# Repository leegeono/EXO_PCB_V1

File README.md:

# EXO_PCB_V1

## Overview
First prototype PCB for motor control experiments.

## Hardware
- ESCON Motor Driver x4
- Teensy 4.1
- Battery Input (3S ~ 6S)
- 5V Regulator
- nano rp2040

 ## Purpose
- Motor control study
- PCB design practice
- Power distribution testing
- Embedded system integration

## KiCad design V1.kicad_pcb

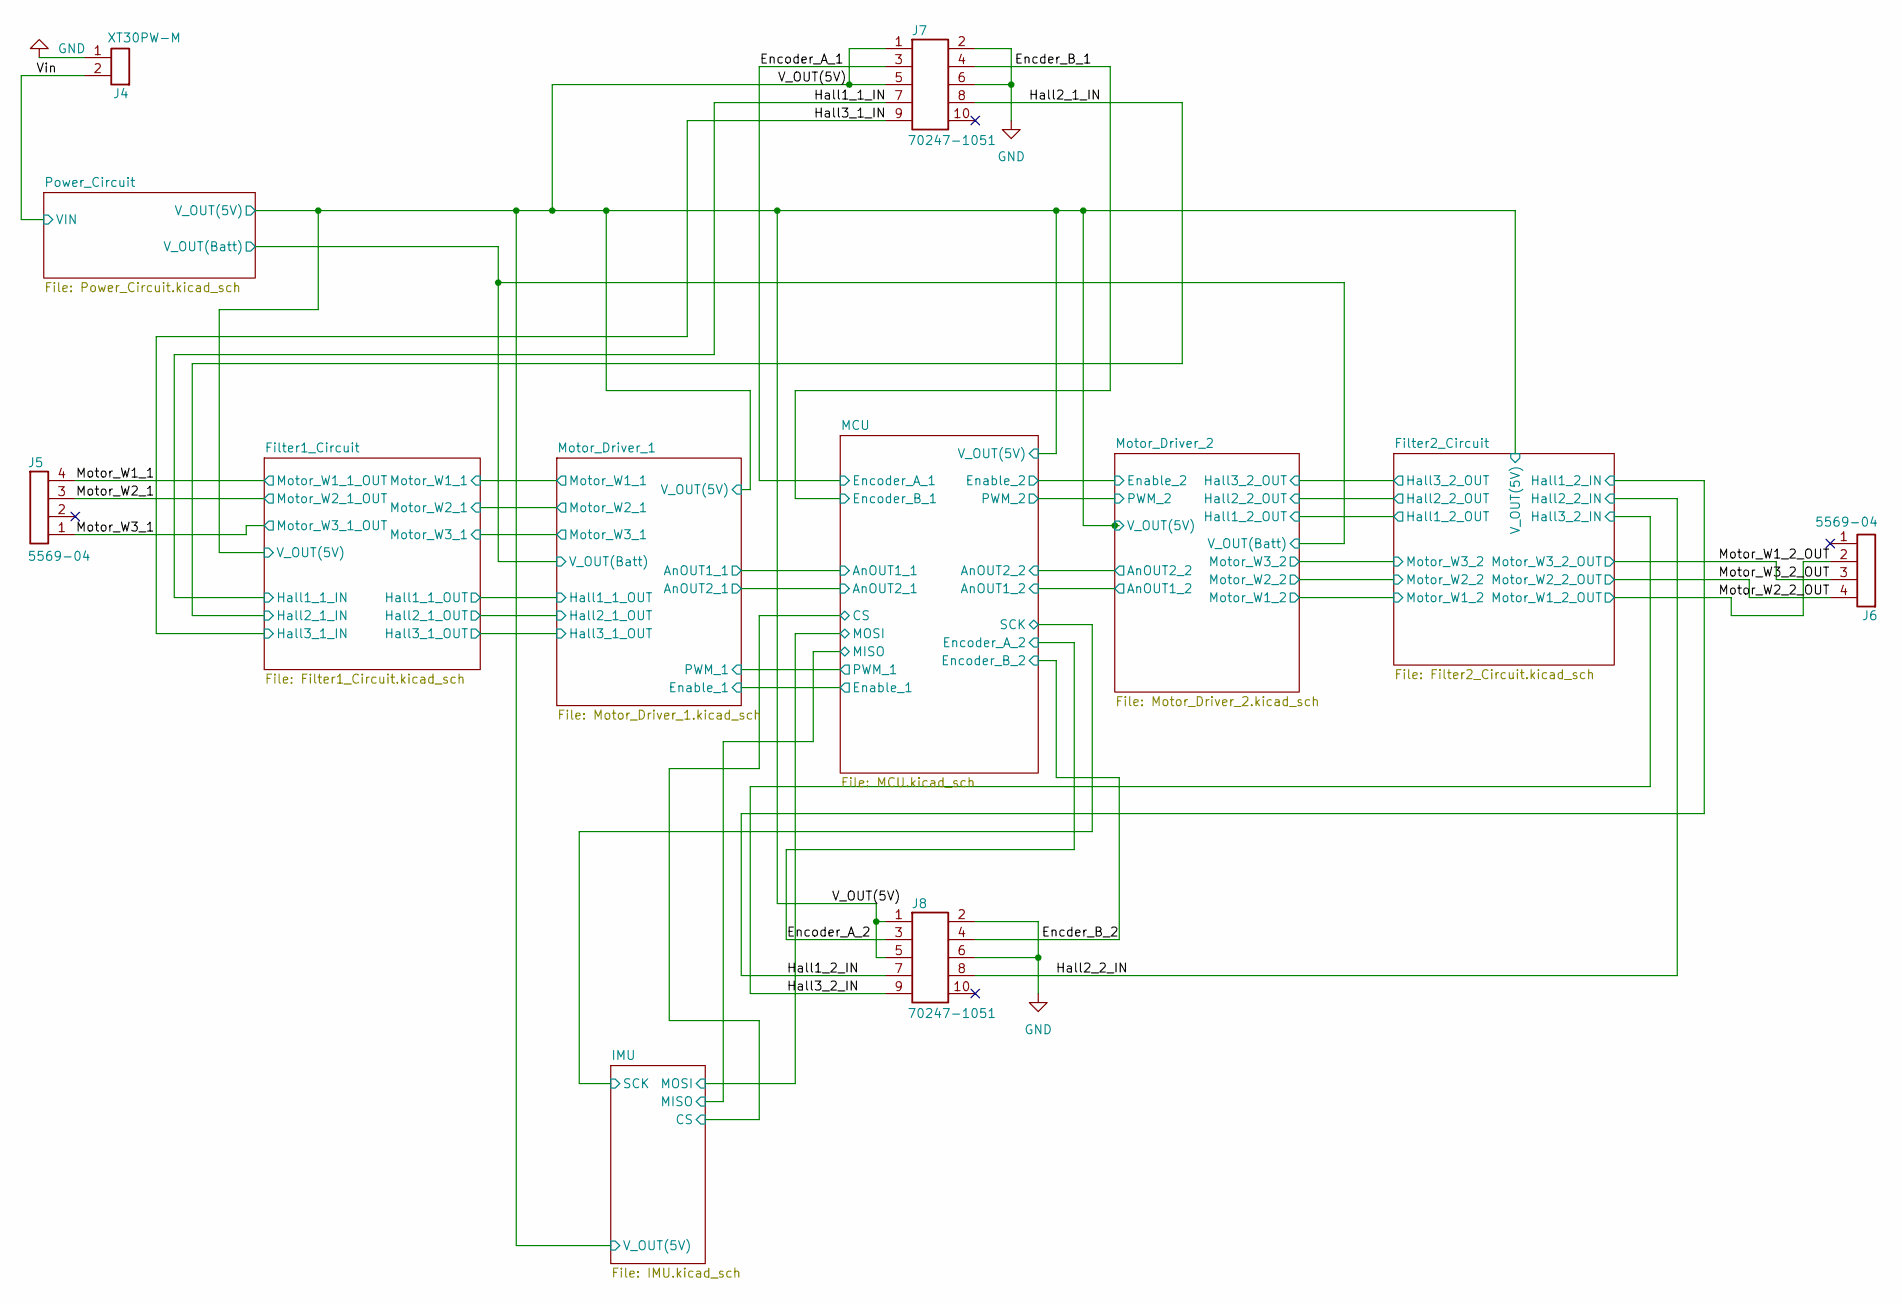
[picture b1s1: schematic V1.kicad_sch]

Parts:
J4: XT30PW-M
J5, J6: 5569-04
J7, J8: 70247-1051

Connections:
/Encder_B_1: J7.4 (Pin_9); also elsewhere on the board
/Encder_B_2: J8.4 (Pin_9); also elsewhere on the board
/Encoder_A_1: J7.3 (Pin_2); also elsewhere on the board
/Encoder_A_2: J8.3 (Pin_2); also elsewhere on the board
/Hall1_1_IN: J7.7 (Pin_4); also elsewhere on the board
/Hall1_2_IN: J8.7 (Pin_4); also elsewhere on the board
/Hall2_1_IN: J7.8 (Pin_7); also elsewhere on the board
/Hall2_2_IN: J8.8 (Pin_7); also elsewhere on the board
/Hall3_1_IN: J7.9; also elsewhere on the board
/Hall3_2_IN: J8.9; also elsewhere on the board
/Motor_W1_1: J5.4; also elsewhere on the board
/Motor_W1_2_OUT: J6.2; also elsewhere on the board
/Motor_W2_1: J5.3; also elsewhere on the board
/Motor_W2_2_OUT: J6.4; also elsewhere on the board
/Motor_W3_1: J5.1; also elsewhere on the board
/Motor_W3_2_OUT: J6.3; also elsewhere on the board
/V_OUT(5V): J7.1, J7.5 (Pin_3), J8.1, J8.5 (Pin_3); also elsewhere on the board
/Vin: J4.2; also elsewhere on the board
GND: J4.1, J7.2 (Pin_10), J7.6 (Pin_8), J8.2 (Pin_10), J8.6 (Pin_8); also elsewhere on the board

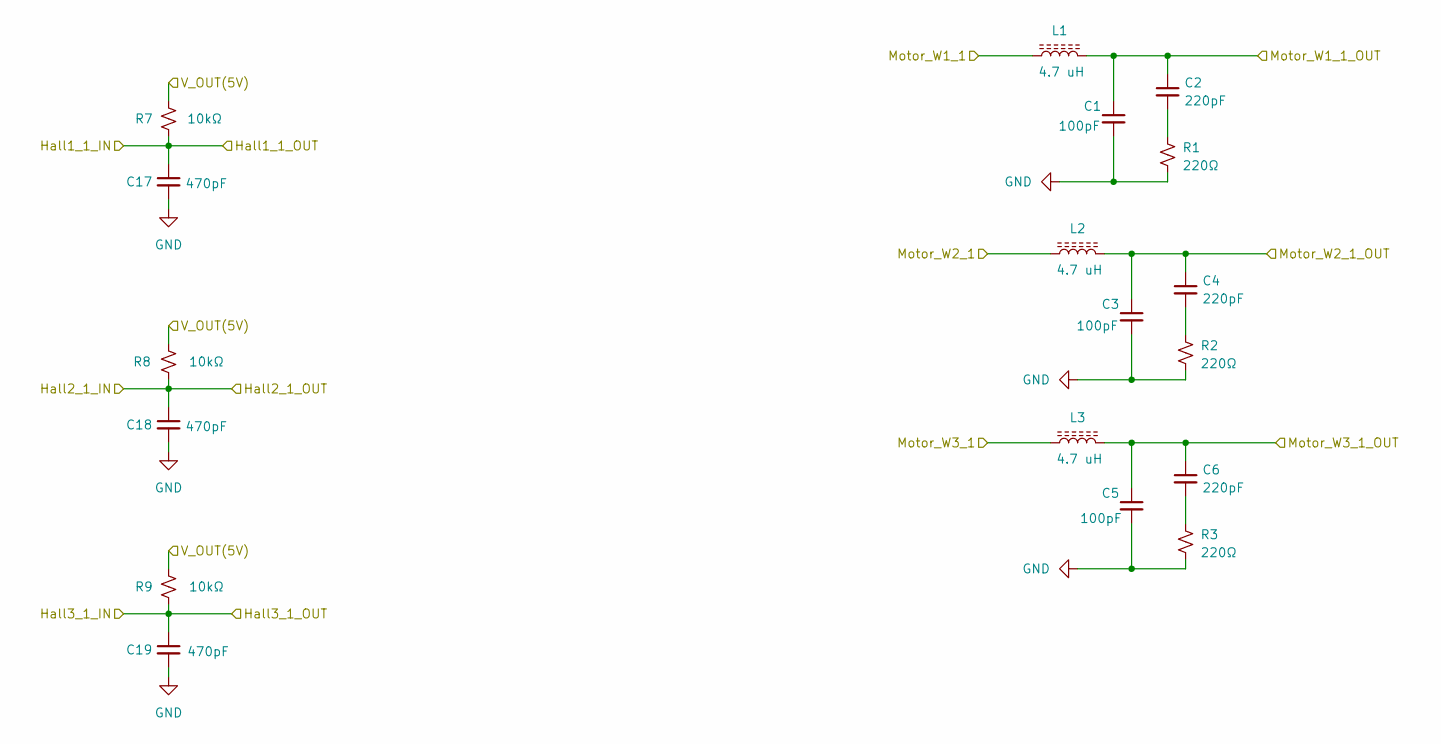
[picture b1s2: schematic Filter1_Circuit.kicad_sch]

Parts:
C1, C3, C5: 100pF; C_0603_1608Metric
C2, C4, C6: 220pF; C_0603_1608Metric
C17, C18, C19: 470pF; C_0603_1608Metric
L1, L2, L3: 4.7 uH; WE-PD_1260_1245_1280_121054
R1, R2, R3: 220Ω; R_1206_3216Metric
R7, R8, R9: 10kΩ; R_0603_1608Metric

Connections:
/Filter1_Circuit/Motor_W1_1: L1.1; also elsewhere on the board
/Filter1_Circuit/Motor_W2_1: L2.1; also elsewhere on the board
/Filter1_Circuit/Motor_W3_1: L3.1; also elsewhere on the board
/Hall1_1_IN: C17.1, R7.2; also elsewhere on the board
/Hall2_1_IN: C18.1, R8.2; also elsewhere on the board
/Hall3_1_IN: C19.1, R9.2; also elsewhere on the board
/Motor_W1_1: C1.1, C2.1, L1.2; also elsewhere on the board
/Motor_W2_1: C3.1, C4.1, L2.2; also elsewhere on the board
/Motor_W3_1: C5.1, C6.1, L3.2; also elsewhere on the board
/V_OUT(5V): R7.1, R8.1, R9.1; also elsewhere on the board
GND: C1.2, C3.2, C5.2, C17.2, C18.2, C19.2, R1.2, R2.2, R3.2; also elsewhere on the board
unnamed: C2.2, R1.1
unnamed: C4.2, R2.1
unnamed: C6.2, R3.1

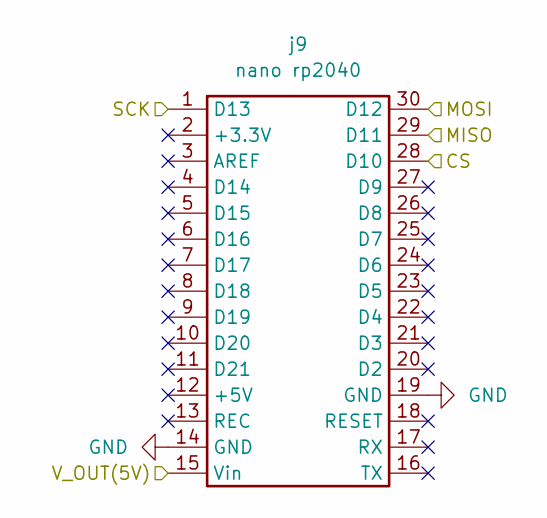
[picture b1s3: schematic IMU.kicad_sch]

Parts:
j9: nano rp2040; nano_rp2040

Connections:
/IMU/CS: j9.28 (D10); also elsewhere on the board
/IMU/MISO: j9.29 (D11); also elsewhere on the board
/IMU/MOSI: j9.30 (D12); also elsewhere on the board
/IMU/SCK: j9.1 (D13); also elsewhere on the board
/V_OUT(5V): j9.15 (Vin); also elsewhere on the board
GND: j9.14 (GND), j9.19 (GND); also elsewhere on the board

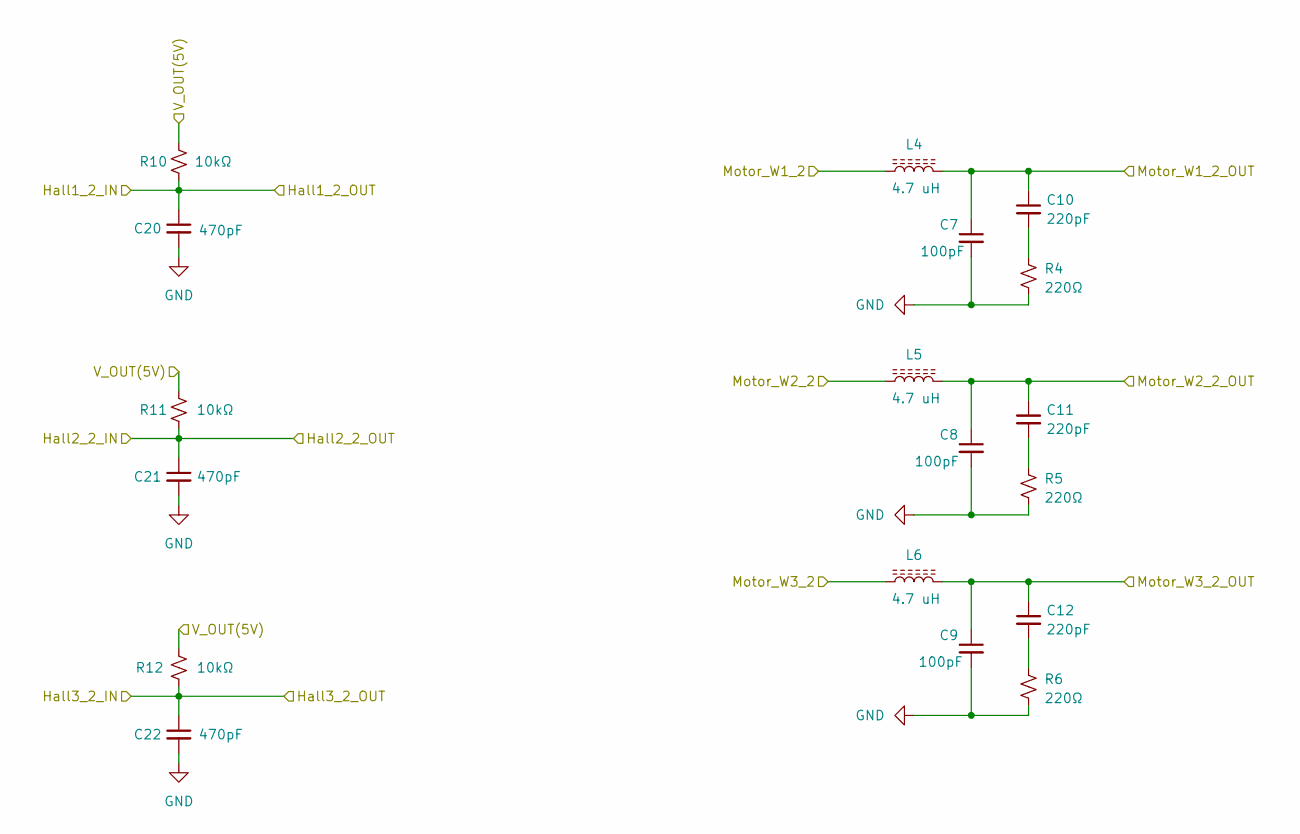
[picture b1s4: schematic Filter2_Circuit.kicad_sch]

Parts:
C7, C8, C9: 100pF; C_0603_1608Metric
C10, C11, C12: 220pF; C_0603_1608Metric
C20, C21, C22: 470pF; C_0603_1608Metric
L4, L5, L6: 4.7 uH; WE-PD_1260_1245_1280_121054
R4, R5, R6: 220Ω; R_1206_3216Metric
R10, R11, R12: 10kΩ; R_0603_1608Metric

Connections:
/Filter2_Circuit/Motor_W1_2: L4.1; also elsewhere on the board
/Filter2_Circuit/Motor_W2_2: L5.1; also elsewhere on the board
/Filter2_Circuit/Motor_W3_2: L6.1; also elsewhere on the board
/Hall1_2_IN: C20.1, R10.2; also elsewhere on the board
/Hall2_2_IN: C21.1, R11.2; also elsewhere on the board
/Hall3_2_IN: C22.1, R12.2; also elsewhere on the board
/Motor_W1_2_OUT: C7.1, C10.1, L4.2; also elsewhere on the board
/Motor_W2_2_OUT: C8.1, C11.1, L5.2; also elsewhere on the board
/Motor_W3_2_OUT: C9.1, C12.1, L6.2; also elsewhere on the board
/V_OUT(5V): R10.1, R11.1, R12.1; also elsewhere on the board
GND: C7.2, C8.2, C9.2, C20.2, C21.2, C22.2, R4.2, R5.2, R6.2; also elsewhere on the board
unnamed: C10.2, R4.1
unnamed: C11.2, R5.1
unnamed: C12.2, R6.1

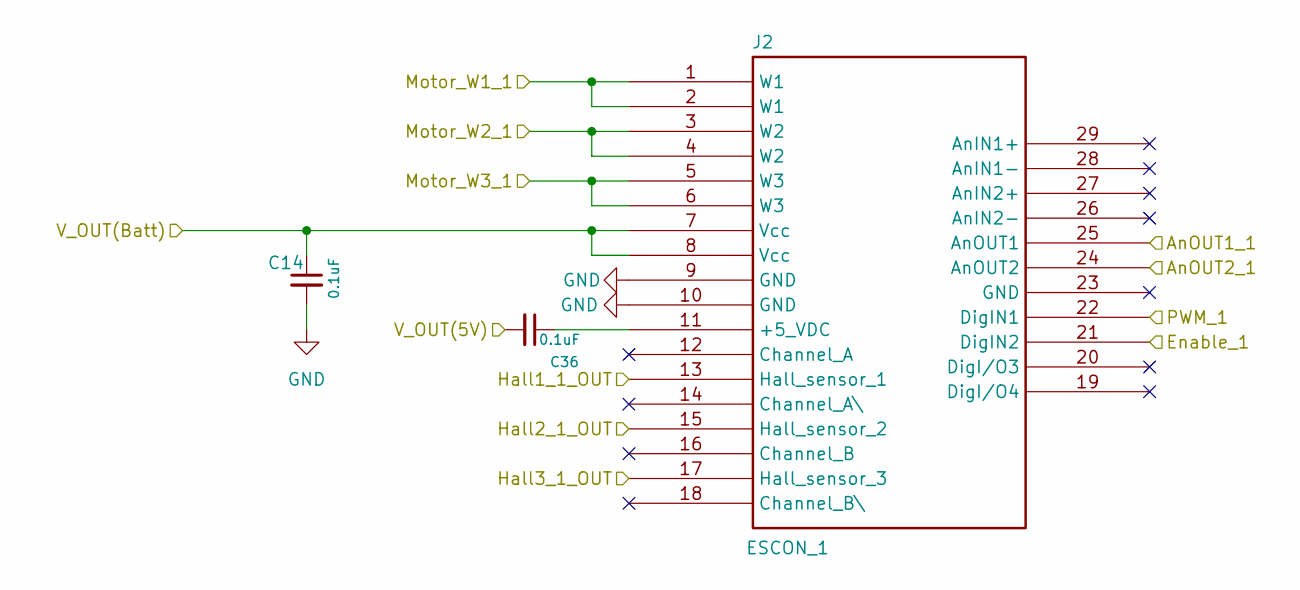
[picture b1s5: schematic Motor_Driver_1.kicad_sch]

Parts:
C14, C36: 0.1uF; C_0603_1608Metric
J2: ESCON_1; Escon 50,8

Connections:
/Filter1_Circuit/Motor_W1_1: J2.1 (W1), J2.2 (W1); also elsewhere on the board
/Filter1_Circuit/Motor_W2_1: J2.3 (W2), J2.4 (W2); also elsewhere on the board
/Filter1_Circuit/Motor_W3_1: J2.5 (W3), J2.6 (W3); also elsewhere on the board
/Hall1_1_IN: J2.13 (Hall_sensor_1); also elsewhere on the board
/Hall2_1_IN: J2.15 (Hall_sensor_2); also elsewhere on the board
/Hall3_1_IN: J2.17 (Hall_sensor_3); also elsewhere on the board
/MCU/AnOUT1_1: J2.25 (AnOUT1); also elsewhere on the board
/MCU/AnOUT2_1: J2.24 (AnOUT2); also elsewhere on the board
/MCU/Enable_1: J2.21 (DigIN2); also elsewhere on the board
/MCU/PWM_1: J2.22 (DigIN1); also elsewhere on the board
/Motor_Driver_1/V_OUT(Batt): C14.1, J2.7 (Vcc), J2.8 (Vcc); also elsewhere on the board
/V_OUT(5V): C36.2; also elsewhere on the board
GND: C14.2, J2.9 (GND), J2.10 (GND); also elsewhere on the board
unnamed: C36.1, J2.11 (+5_VDC)

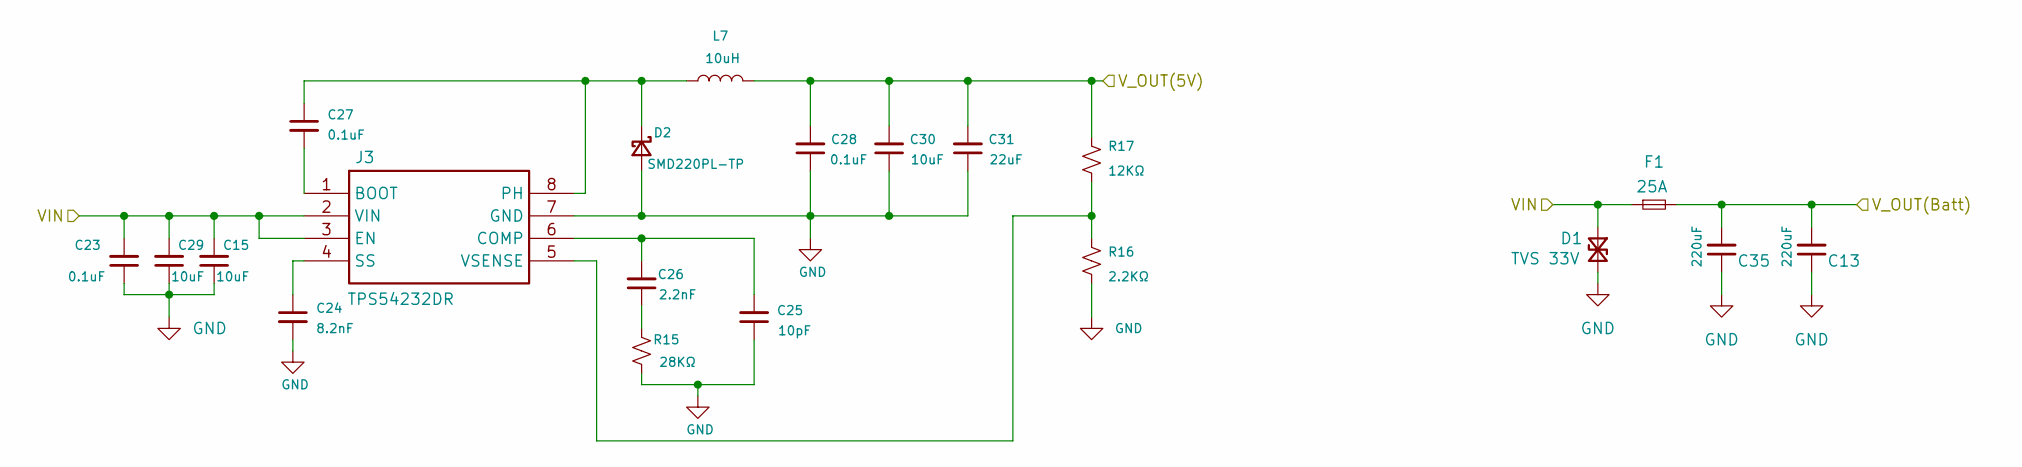
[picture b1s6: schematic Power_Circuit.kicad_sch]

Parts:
C13, C35: 220uF; UPM1J221MHD
C15, C29, C30: 10uF; C_0805_2012Metric
C23, C27, C28: 0.1uF; C_0603_1608Metric
C24: 8.2nF; C_0603_1608Metric
C25: 10pF; C_0603_1608Metric
C26: 2.2nF; C_0603_1608Metric
C31: 22uF; C_0805_2012Metric
D1: TVS 33V; SMBJ33A
D2: SMD220PL-TP; SMD220PLTP
F1: 25A; 0683G925001
J3: TPS54232DR; TPS54232; Mouser Part Number 595-TPS54232DR
L7: 10uH; SRN5040TA100MP
R15: 28KΩ; R_0603_1608Metric
R16: 2.2KΩ; R_0603_1608Metric
R17: 12KΩ; R_0603_1608Metric

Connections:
/Motor_Driver_1/V_OUT(Batt): C13.2, C35.2, F1.2; also elsewhere on the board
/V_OUT(5V): C28.2, C30.2, C31.2, L7.2, R17.1; also elsewhere on the board
/Vin: C15.2, C23.2, C29.2, D1.1 (A1), F1.1, J3.2 (VIN), J3.3 (EN); also elsewhere on the board
GND: C13.1, C15.1, C23.1, C24.2, C25.1, C28.1, C29.1, C30.1, C31.1, C35.1, D1.2 (A2), D2.2 (A), J3.7 (GND), R15.1, R16.2; also elsewhere on the board
unnamed: C26.1, R15.2
unnamed: C27.1, D2.1 (K), J3.8 (PH), L7.1
unnamed: C27.2, J3.1 (BOOT)
unnamed: C25.2, C26.2, J3.6 (COMP)
unnamed: C24.1, J3.4 (SS)
unnamed: J3.5 (VSENSE), R16.1, R17.2

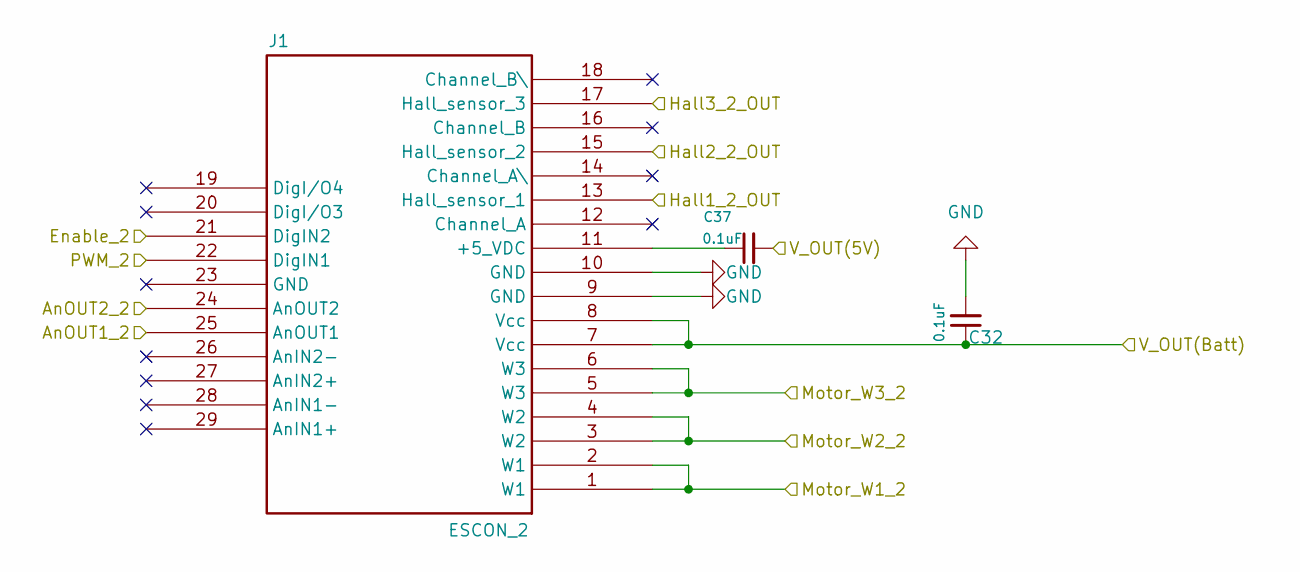
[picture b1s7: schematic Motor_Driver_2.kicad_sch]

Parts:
C32, C37: 0.1uF; C_0603_1608Metric
J1: ESCON_2; Escon 50,8

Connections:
/Filter2_Circuit/Motor_W1_2: J1.1 (W1), J1.2 (W1); also elsewhere on the board
/Filter2_Circuit/Motor_W2_2: J1.3 (W2), J1.4 (W2); also elsewhere on the board
/Filter2_Circuit/Motor_W3_2: J1.5 (W3), J1.6 (W3); also elsewhere on the board
/Hall1_2_IN: J1.13 (Hall_sensor_1); also elsewhere on the board
/Hall2_2_IN: J1.15 (Hall_sensor_2); also elsewhere on the board
/Hall3_2_IN: J1.17 (Hall_sensor_3); also elsewhere on the board
/MCU/AnOUT1_2: J1.25 (AnOUT1); also elsewhere on the board
/MCU/AnOUT2_2: J1.24 (AnOUT2); also elsewhere on the board
/MCU/Enable_2: J1.21 (DigIN2); also elsewhere on the board
/MCU/PWM_2: J1.22 (DigIN1); also elsewhere on the board
/Motor_Driver_1/V_OUT(Batt): C32.1, J1.7 (Vcc), J1.8 (Vcc); also elsewhere on the board
/V_OUT(5V): C37.2; also elsewhere on the board
GND: C32.2, J1.9 (GND), J1.10 (GND); also elsewhere on the board
unnamed: C37.1, J1.11 (+5_VDC)

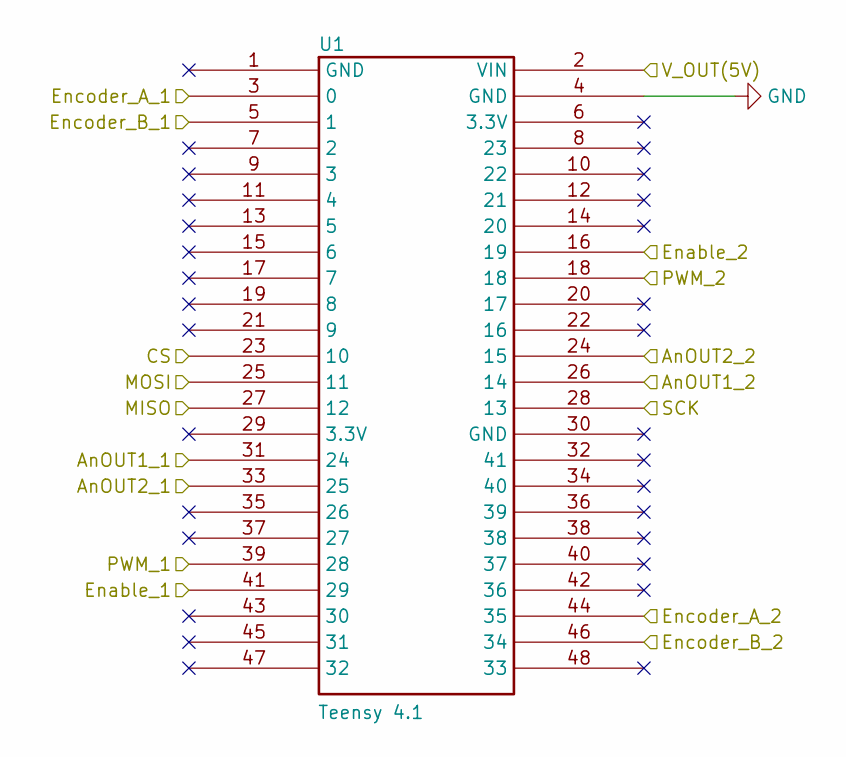
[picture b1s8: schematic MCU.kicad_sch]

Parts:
U1: Teensy 4.1; Teensy41

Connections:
/Encder_B_1: U1.5 (1); also elsewhere on the board
/Encder_B_2: U1.46 (34); also elsewhere on the board
/Encoder_A_1: U1.3 (0); also elsewhere on the board
/Encoder_A_2: U1.44 (35); also elsewhere on the board
/IMU/CS: U1.23 (10); also elsewhere on the board
/IMU/MISO: U1.27 (12); also elsewhere on the board
/IMU/MOSI: U1.25 (11); also elsewhere on the board
/IMU/SCK: U1.28 (13); also elsewhere on the board
/MCU/AnOUT1_1: U1.31 (24); also elsewhere on the board
/MCU/AnOUT1_2: U1.26 (14); also elsewhere on the board
/MCU/AnOUT2_1: U1.33 (25); also elsewhere on the board
/MCU/AnOUT2_2: U1.24 (15); also elsewhere on the board
/MCU/Enable_1: U1.41 (29); also elsewhere on the board
/MCU/Enable_2: U1.16 (19); also elsewhere on the board
/MCU/PWM_1: U1.39 (28); also elsewhere on the board
/MCU/PWM_2: U1.18; also elsewhere on the board
/V_OUT(5V): U1.2 (VIN); also elsewhere on the board
GND: U1.4 (GND); also elsewhere on the board

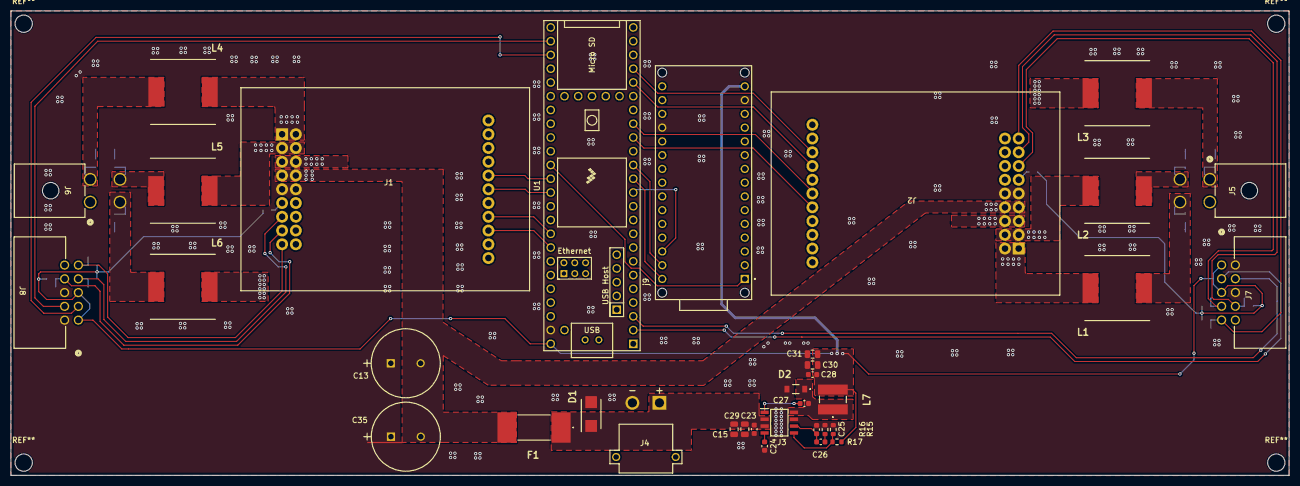
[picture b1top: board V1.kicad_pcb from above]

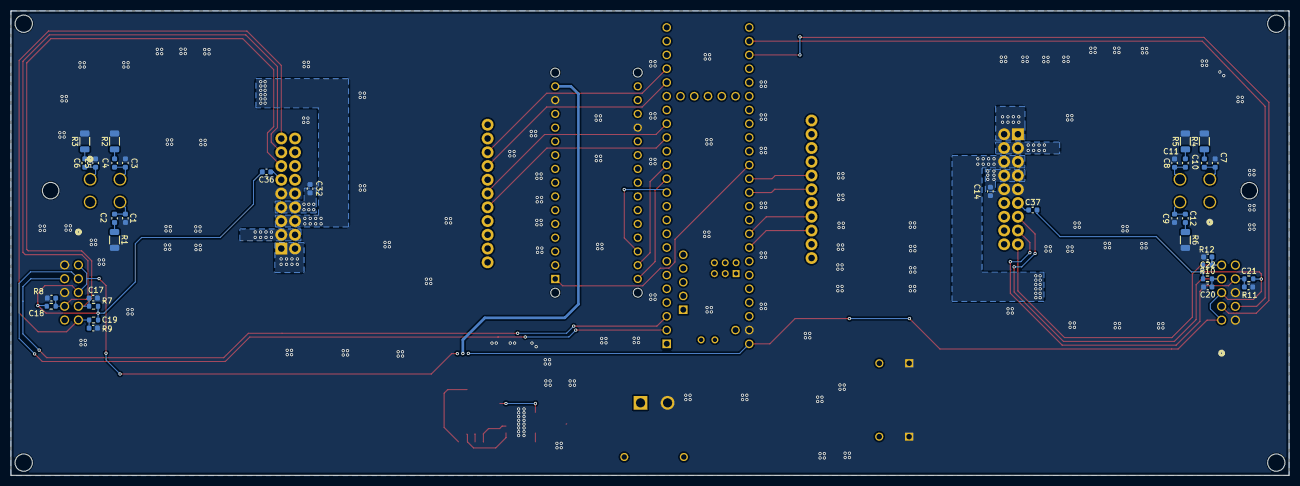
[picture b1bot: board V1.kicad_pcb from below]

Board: 2 copper layers, 236.0 x 85.7 mm, 69 parts (34 on the bottom side), 52 nets.
